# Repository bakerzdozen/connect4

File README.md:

# connect4

## About

4-in-a-line ("Connect 4" by Hasbro) is a popular two-player table game played with red and yellow chips for player 1 and player 2, respectively. It is played on a 7x6 board, where the objective is to connect four of your coloured chips in a row - be that horizontal, vertical or diagonal. 

This project aims to recreate the joy of 4-in-a-line with a modern twist, allowing for solo play against the "computer" (a very basic algorithm). Both the hardware and firmware are included in this repository to allow you to create your own variants or to make the exact same one yourself!

Originally, this project was a Christmas gift for my family and friends, but I have now made it open-source so anyone can make their own, or modify it to make it even better!

## Making Your Own

If you intend to create your own, you will need - at very least - the following:

- STM Cube IDE
- Pre-compiled firmware
- Fully assembled circuit board (I recommend JLC PCB)

## Improvements

If you have suggestions for how to make this project better, please let me know! The best way is through creating your own branch and making the modifications you see fit. If they are sensible and enhance the project in some meaningful way, I will be happy to merge your modifications to the main branch!

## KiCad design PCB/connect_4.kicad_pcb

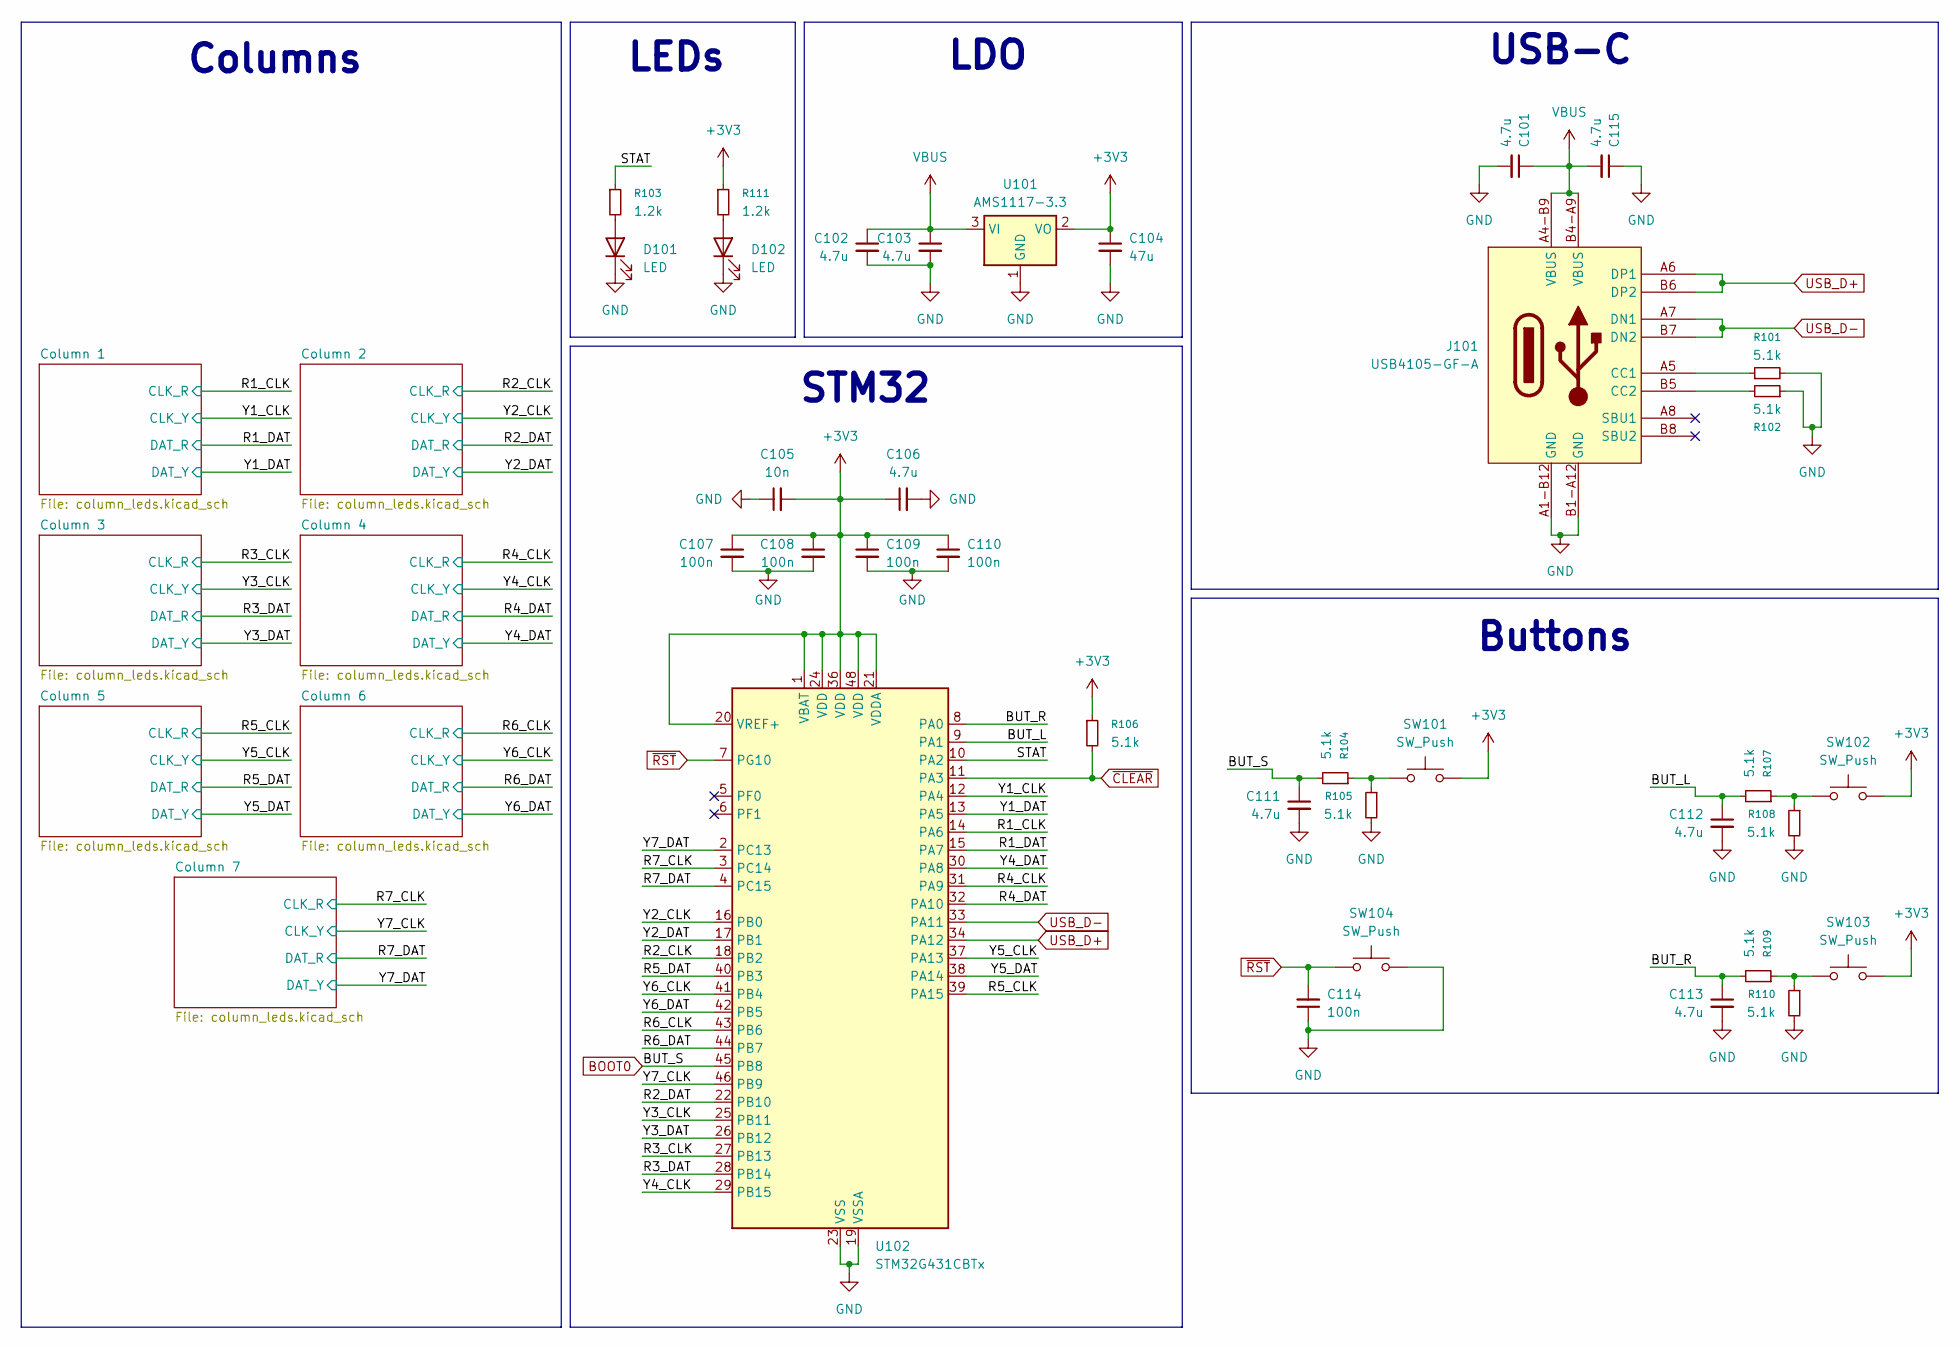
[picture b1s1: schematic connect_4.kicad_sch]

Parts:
C101, C102, C103, C106, C111, C112, C113, C115: 4.7u; C_0603_1608Metric; Manufacturer Part Number C69335
C104: 47u; C_1206_3216Metric; Manufacturer Part Number C403725
C105: 10n; C_0603_1608Metric; Manufacturer Part Number C1589
C107, C108, C109, C110, C114: 100n; C_0603_1608Metric; Manufacturer Part Number C1591
D101, D102: LED; D_0603_1608Metric; Manufacturer Part Number C126319
J101: USB4105-GF-A; USB4105_GCT; Manufacturer Part Number C2765186
R101, R102, R104, R105, R106, R107, R108, R109, R110: 5.1k; R_0603_1608Metric; Manufacturer Part Number C105580
R103, R111: 1.2k; R_0603_1608Metric; Manufacturer Part Number C114605
SW101, SW102, SW103, SW104: SW_Push; SW_Push_1P1T_NO_CK_KSC9xxG; Manufacturer Part Number C2837531
U101: AMS1117-3.3; SOT-223-3_TabPin2; Manufacturer Part Number C6186
U102: STM32G431CBTx; LQFP-48_7x7mm_P0.5mm; Manufacturer Part Number C529355

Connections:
+3V3: C104.1, C105.2, C106.1, C107.1, C108.1, C109.1, C110.1, R106.1, R111.1, SW101.2, SW102.2, SW103.2, U101.2 (VO), U102.1 (VBAT), U102.20 (VREF+), U102.21 (VDDA), U102.24 (VDD), U102.36 (VDD), U102.48 (VDD); also elsewhere on the board
/BUT_L: C112.1, R107.2, U102.9 (PA1)
/BUT_R: C113.1, R109.2, U102.8 (PA0)
/R1_CLK: U102.14 (PA6); also elsewhere on the board
/R1_DAT: U102.15 (PA7); also elsewhere on the board
/R2_CLK: U102.18 (PB2); also elsewhere on the board
/R2_DAT: U102.22 (PB10); also elsewhere on the board
/R3_CLK: U102.27 (PB13); also elsewhere on the board
/R3_DAT: U102.28 (PB14); also elsewhere on the board
/R4_CLK: U102.31 (PA9); also elsewhere on the board
/R4_DAT: U102.32 (PA10); also elsewhere on the board
/R5_CLK: U102.39 (PA15); also elsewhere on the board
/R5_DAT: U102.40 (PB3); also elsewhere on the board
/R6_CLK: U102.43 (PB6); also elsewhere on the board
/R6_DAT: U102.44 (PB7); also elsewhere on the board
/R7_CLK: U102.3 (PC14); also elsewhere on the board
/R7_DAT: U102.4 (PC15); also elsewhere on the board
/STAT: R103.1, U102.10 (PA2)
/Y1_CLK: U102.12 (PA4); also elsewhere on the board
/Y1_DAT: U102.13 (PA5); also elsewhere on the board
/Y2_CLK: U102.16 (PB0); also elsewhere on the board
/Y2_DAT: U102.17 (PB1); also elsewhere on the board
/Y3_CLK: U102.25 (PB11); also elsewhere on the board
/Y3_DAT: U102.26 (PB12); also elsewhere on the board
/Y4_CLK: U102.29 (PB15); also elsewhere on the board
/Y4_DAT: U102.30 (PA8); also elsewhere on the board
/Y5_CLK: U102.37 (PA13); also elsewhere on the board
/Y5_DAT: U102.38 (PA14); also elsewhere on the board
/Y6_CLK: U102.41 (PB4); also elsewhere on the board
/Y6_DAT: U102.42 (PB5); also elsewhere on the board
/Y7_CLK: U102.46 (PB9); also elsewhere on the board
/Y7_DAT: U102.2 (PC13); also elsewhere on the board
BOOT0: C111.1, R104.2, U102.45 (PB8)
GND: C101.2, C102.2, C103.2, C104.2, C105.1, C106.2, C107.2, C108.2, C109.2, C110.2, C111.2, C112.2, C113.2, C114.1, C115.1, D101.1 (K), D102.1 (K), J101.A1-B12 (GND), J101.B1-A12 (GND), R101.2, R102.1, R105.2, R108.2, R110.2, SW104.2, U101.1 (GND), U102.19 (VSSA), U102.23 (VSS), U102.35 (VSS), U102.47 (VSS); also elsewhere on the board
unnamed: D101.2 (A), R103.2
unnamed: D102.2 (A), R111.2
unnamed: J101.A5 (CC1), R101.1
unnamed: J101.B5 (CC2), R102.2
unnamed: R104.1, R105.1, SW101.1
unnamed: R107.1, R108.1, SW102.1
unnamed: R109.1, R110.1, SW103.1
USB_D+: J101.A6 (DP1), J101.B6 (DP2), U102.34 (PA12)
USB_D-: J101.A7 (DN1), J101.B7 (DN2), U102.33 (PA11)
VBUS: C101.1, C102.1, C103.1, C115.2, J101.A4-B9 (VBUS), J101.B4-A9 (VBUS), U101.3 (VI)
~CLEAR: R106.2, U102.11 (PA3); also elsewhere on the board
~RST: C114.2, SW104.1, U102.7 (PG10)

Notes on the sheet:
Buttons
USB-C
LDO
LEDs
STM32
Columns

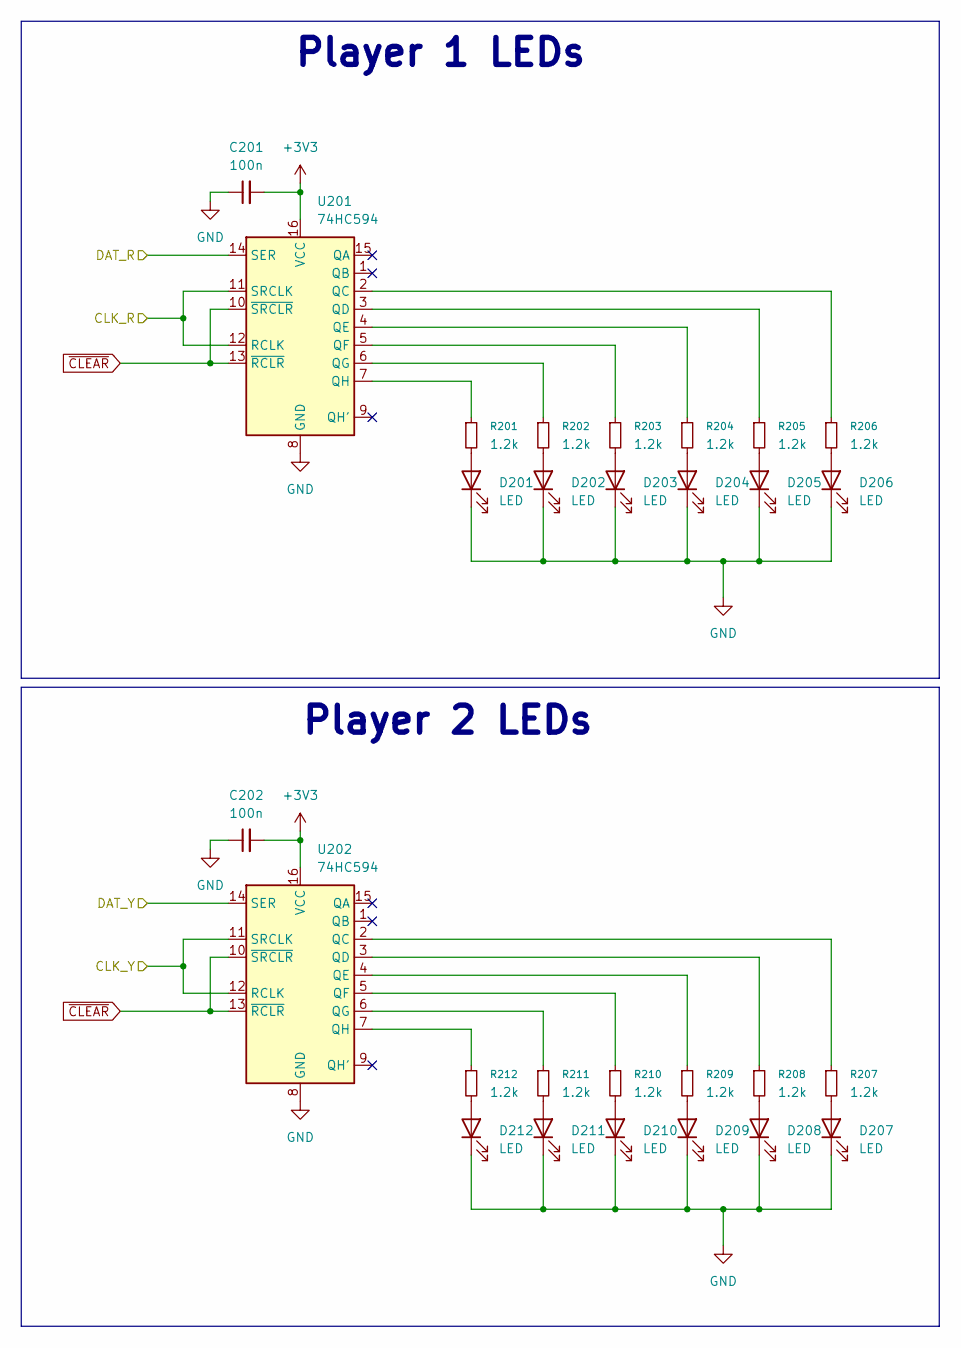
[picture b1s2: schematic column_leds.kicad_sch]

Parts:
C201, C202: 100n; C_0603_1608Metric; Manufacturer Part Number C1591
D201, D202, D203, D204, D205, D206: LED; D_0603_1608Metric; Manufacturer Part Number C79636
D207, D208, D209, D210, D211, D212: LED; D_0603_1608Metric; Manufacturer Part Number C122984
R201, R202, R203, R204, R205, R206, R207, R208, R209, R210, R211, R212: 1.2k; R_0603_1608Metric; Manufacturer Part Number C114605
U201, U202: 74HC594; SOIC-16W_5.3x10.2mm_P1.27mm; Manufacturer Part Number C91727

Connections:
+3V3: C201.2, C202.2, U201.16 (VCC), U202.16 (VCC); also elsewhere on the board
/R1_CLK: U201.11 (SRCLK), U201.12 (RCLK); also elsewhere on the board
/R1_DAT: U201.14 (SER); also elsewhere on the board
/Y1_CLK: U202.11 (SRCLK), U202.12 (RCLK); also elsewhere on the board
/Y1_DAT: U202.14 (SER); also elsewhere on the board
GND: C201.1, C202.1, D201.1 (K), D202.1 (K), D203.1 (K), D204.1 (K), D205.1 (K), D206.1 (K), D207.1 (K), D208.1 (K), D209.1 (K), D210.1 (K), D211.1 (K), D212.1 (K), U201.8 (GND), U202.8 (GND); also elsewhere on the board
unnamed: D201.2 (A), R201.2
unnamed: D202.2 (A), R202.2
unnamed: D203.2 (A), R203.2
unnamed: D204.2 (A), R204.2
unnamed: D205.2 (A), R205.2
unnamed: D206.2 (A), R206.2
unnamed: D207.2 (A), R207.2
unnamed: D208.2 (A), R208.2
unnamed: D209.2 (A), R209.2
unnamed: D210.2 (A), R210.2
unnamed: D211.2 (A), R211.2
unnamed: D212.2 (A), R212.2
unnamed: R206.1, U201.2 (QC)
unnamed: R205.1, U201.3 (QD)
unnamed: R204.1, U201.4 (QE)
unnamed: R203.1, U201.5 (QF)
unnamed: R202.1, U201.6 (QG)
unnamed: R201.1, U201.7 (QH)
unnamed: R207.1, U202.2 (QC)
unnamed: R208.1, U202.3 (QD)
unnamed: R209.1, U202.4 (QE)
unnamed: R210.1, U202.5 (QF)
unnamed: R211.1, U202.6 (QG)
unnamed: R212.1, U202.7 (QH)
~CLEAR: U201.10 (~SRCLR), U201.13 (~RCLR), U202.10 (~SRCLR), U202.13 (~RCLR); also elsewhere on the board

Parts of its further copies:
C301, C302, C401, C402, C501, C502, C601, C602, C701, C702, C801, C802: 100n; C_0603_1608Metric; Manufacturer Part Number C1591
D301, D302, D303, D304, D305, D306, D401, D402, D403, D404, D405, D406, D501, D502, D503, D504, D505, D506, D601, D602, D603, D604, D605, D606, D701, D702, D703, D704, D705, D706, D801, D802, D803, D804, D805, D806: LED; D_0603_1608Metric; Manufacturer Part Number C79636
D307, D308, D309, D310, D311, D312, D407, D408, D409, D410, D411, D412, D507, D508, D509, D510, D511, D512, D607, D608, D609, D610, D611, D612, D707, D708, D709, D710, D711, D712, D807, D808, D809, D810, D811, D812: LED; D_0603_1608Metric; Manufacturer Part Number C122984
R301, R302, R303, R304, R305, R306, R307, R308, R309, R310, R311, R312, R401, R402, R403, R404, R405, R406, R407, R408, R409, R410, R411, R412, R501, R502, R503, R504, R505, R506, R507, R508, R509, R510, R511, R512, R601, R602, R603, R604, R605, R606, R607, R608, R609, R610, R611, R612, R701, R702, R703, R704, R705, R706, R707, R708, R709, R710, R711, R712, R801, R802, R803, R804, R805, R806, R807, R808, R809, R810, R811, R812: 1.2k; R_0603_1608Metric; Manufacturer Part Number C114605
U301, U302, U401, U402, U501, U502, U601, U602, U701, U702, U801, U802: 74HC594; SOIC-16W_5.3x10.2mm_P1.27mm; Manufacturer Part Number C91727

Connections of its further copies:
+3V3: C301.2, C302.2, C401.2, C402.2, C501.2, C502.2, C601.2, C602.2, C701.2, C702.2, C801.2, C802.2, U301.16 (VCC), U302.16 (VCC), U401.16 (VCC), U402.16 (VCC), U501.16 (VCC), U502.16 (VCC), U601.16 (VCC), U602.16 (VCC), U701.16 (VCC), U702.16 (VCC), U801.16 (VCC), U802.16 (VCC); also elsewhere on the board
/R2_CLK: U301.11 (SRCLK), U301.12 (RCLK); also elsewhere on the board
/R2_DAT: U301.14 (SER); also elsewhere on the board
/R3_CLK: U401.11 (SRCLK), U401.12 (RCLK); also elsewhere on the board
/R3_DAT: U401.14 (SER); also elsewhere on the board
/R4_CLK: U501.11 (SRCLK), U501.12 (RCLK); also elsewhere on the board
/R4_DAT: U501.14 (SER); also elsewhere on the board
/R5_CLK: U601.11 (SRCLK), U601.12 (RCLK); also elsewhere on the board
/R5_DAT: U601.14 (SER); also elsewhere on the board
/R6_CLK: U701.11 (SRCLK), U701.12 (RCLK); also elsewhere on the board
/R6_DAT: U701.14 (SER); also elsewhere on the board
/R7_CLK: U801.11 (SRCLK), U801.12 (RCLK); also elsewhere on the board
/R7_DAT: U801.14 (SER); also elsewhere on the board
/Y2_CLK: U302.11 (SRCLK), U302.12 (RCLK); also elsewhere on the board
/Y2_DAT: U302.14 (SER); also elsewhere on the board
/Y3_CLK: U402.11 (SRCLK), U402.12 (RCLK); also elsewhere on the board
/Y3_DAT: U402.14 (SER); also elsewhere on the board
/Y4_CLK: U502.11 (SRCLK), U502.12 (RCLK); also elsewhere on the board
/Y4_DAT: U502.14 (SER); also elsewhere on the board
/Y5_CLK: U602.11 (SRCLK), U602.12 (RCLK); also elsewhere on the board
/Y5_DAT: U602.14 (SER); also elsewhere on the board
/Y6_CLK: U702.11 (SRCLK), U702.12 (RCLK); also elsewhere on the board
/Y6_DAT: U702.14 (SER); also elsewhere on the board
/Y7_CLK: U802.11 (SRCLK), U802.12 (RCLK); also elsewhere on the board
/Y7_DAT: U802.14 (SER); also elsewhere on the board
GND: C301.1, C302.1, C401.1, C402.1, C501.1, C502.1, C601.1, C602.1, C701.1, C702.1, C801.1, C802.1, D301.1 (K), D302.1 (K), D303.1 (K), D304.1 (K), D305.1 (K), D306.1 (K), D307.1 (K), D308.1 (K), D309.1 (K), D310.1 (K), D311.1 (K), D312.1 (K), D401.1 (K), D402.1 (K), D403.1 (K), D404.1 (K), D405.1 (K), D406.1 (K), D407.1 (K), D408.1 (K), D409.1 (K), D410.1 (K), D411.1 (K), D412.1 (K), D501.1 (K), D502.1 (K), D503.1 (K), D504.1 (K), D505.1 (K), D506.1 (K), D507.1 (K), D508.1 (K), D509.1 (K), D510.1 (K), D511.1 (K), D512.1 (K), D601.1 (K), D602.1 (K), D603.1 (K), D604.1 (K), D605.1 (K), D606.1 (K), D607.1 (K), D608.1 (K), D609.1 (K), D610.1 (K), D611.1 (K), D612.1 (K), D701.1 (K), D702.1 (K), D703.1 (K), D704.1 (K), D705.1 (K), D706.1 (K), D707.1 (K), D708.1 (K), D709.1 (K), D710.1 (K), D711.1 (K), D712.1 (K), D801.1 (K), D802.1 (K), D803.1 (K), D804.1 (K), D805.1 (K), D806.1 (K), D807.1 (K), D808.1 (K), D809.1 (K), D810.1 (K), D811.1 (K), D812.1 (K), U301.8 (GND), U302.8 (GND), U401.8 (GND), U402.8 (GND), U501.8 (GND), U502.8 (GND), U601.8 (GND), U602.8 (GND), U701.8 (GND), U702.8 (GND), U801.8 (GND), U802.8 (GND); also elsewhere on the board
unnamed: D301.2 (A), R301.2
unnamed: D302.2 (A), R302.2
unnamed: D303.2 (A), R303.2
unnamed: D304.2 (A), R304.2
unnamed: D305.2 (A), R305.2
unnamed: D306.2 (A), R306.2
unnamed: D307.2 (A), R307.2
unnamed: D308.2 (A), R308.2
unnamed: D309.2 (A), R309.2
unnamed: D310.2 (A), R310.2
unnamed: D311.2 (A), R311.2
unnamed: D312.2 (A), R312.2
unnamed: D401.2 (A), R401.2
unnamed: D402.2 (A), R402.2
unnamed: D403.2 (A), R403.2
unnamed: D404.2 (A), R404.2
unnamed: D405.2 (A), R405.2
unnamed: D406.2 (A), R406.2
unnamed: D407.2 (A), R407.2
unnamed: D408.2 (A), R408.2
unnamed: D409.2 (A), R409.2
unnamed: D410.2 (A), R410.2
unnamed: D411.2 (A), R411.2
unnamed: D412.2 (A), R412.2
unnamed: D501.2 (A), R501.2
unnamed: D502.2 (A), R502.2
unnamed: D503.2 (A), R503.2
unnamed: D504.2 (A), R504.2
unnamed: D505.2 (A), R505.2
unnamed: D506.2 (A), R506.2
unnamed: D507.2 (A), R507.2
unnamed: D508.2 (A), R508.2
unnamed: D509.2 (A), R509.2
unnamed: D510.2 (A), R510.2
unnamed: D511.2 (A), R511.2
unnamed: D512.2 (A), R512.2
unnamed: D601.2 (A), R601.2
unnamed: D602.2 (A), R602.2
unnamed: D603.2 (A), R603.2
unnamed: D604.2 (A), R604.2
unnamed: D605.2 (A), R605.2
unnamed: D606.2 (A), R606.2
unnamed: D607.2 (A), R607.2
unnamed: D608.2 (A), R608.2
unnamed: D609.2 (A), R609.2
unnamed: D610.2 (A), R610.2
unnamed: D611.2 (A), R611.2
unnamed: D612.2 (A), R612.2
unnamed: D701.2 (A), R701.2
unnamed: D702.2 (A), R702.2
unnamed: D703.2 (A), R703.2
unnamed: D704.2 (A), R704.2
unnamed: D705.2 (A), R705.2
unnamed: D706.2 (A), R706.2
unnamed: D707.2 (A), R707.2
unnamed: D708.2 (A), R708.2
unnamed: D709.2 (A), R709.2
unnamed: D710.2 (A), R710.2
unnamed: D711.2 (A), R711.2
unnamed: D712.2 (A), R712.2
unnamed: D801.2 (A), R801.2
unnamed: D802.2 (A), R802.2
unnamed: D803.2 (A), R803.2
unnamed: D804.2 (A), R804.2
unnamed: D805.2 (A), R805.2
unnamed: D806.2 (A), R806.2
unnamed: D807.2 (A), R807.2
unnamed: D808.2 (A), R808.2
unnamed: D809.2 (A), R809.2
unnamed: D810.2 (A), R810.2
unnamed: D811.2 (A), R811.2
unnamed: D812.2 (A), R812.2
unnamed: R306.1, U301.2 (QC)
unnamed: R305.1, U301.3 (QD)
unnamed: R304.1, U301.4 (QE)
unnamed: R303.1, U301.5 (QF)
unnamed: R302.1, U301.6 (QG)
unnamed: R301.1, U301.7 (QH)
unnamed: R307.1, U302.2 (QC)
unnamed: R308.1, U302.3 (QD)
unnamed: R309.1, U302.4 (QE)
unnamed: R310.1, U302.5 (QF)
unnamed: R311.1, U302.6 (QG)
unnamed: R312.1, U302.7 (QH)
unnamed: R406.1, U401.2 (QC)
unnamed: R405.1, U401.3 (QD)
unnamed: R404.1, U401.4 (QE)
unnamed: R403.1, U401.5 (QF)
unnamed: R402.1, U401.6 (QG)
unnamed: R401.1, U401.7 (QH)
unnamed: R407.1, U402.2 (QC)
unnamed: R408.1, U402.3 (QD)
unnamed: R409.1, U402.4 (QE)
unnamed: R410.1, U402.5 (QF)
unnamed: R411.1, U402.6 (QG)
unnamed: R412.1, U402.7 (QH)
unnamed: R506.1, U501.2 (QC)
unnamed: R505.1, U501.3 (QD)
unnamed: R504.1, U501.4 (QE)
unnamed: R503.1, U501.5 (QF)
unnamed: R502.1, U501.6 (QG)
unnamed: R501.1, U501.7 (QH)
unnamed: R507.1, U502.2 (QC)
unnamed: R508.1, U502.3 (QD)
unnamed: R509.1, U502.4 (QE)
unnamed: R510.1, U502.5 (QF)
unnamed: R511.1, U502.6 (QG)
unnamed: R512.1, U502.7 (QH)
unnamed: R606.1, U601.2 (QC)
unnamed: R605.1, U601.3 (QD)
unnamed: R604.1, U601.4 (QE)
unnamed: R603.1, U601.5 (QF)
unnamed: R602.1, U601.6 (QG)
unnamed: R601.1, U601.7 (QH)
unnamed: R607.1, U602.2 (QC)
unnamed: R608.1, U602.3 (QD)
unnamed: R609.1, U602.4 (QE)
unnamed: R610.1, U602.5 (QF)
unnamed: R611.1, U602.6 (QG)
unnamed: R612.1, U602.7 (QH)
unnamed: R706.1, U701.2 (QC)
unnamed: R705.1, U701.3 (QD)
unnamed: R704.1, U701.4 (QE)
unnamed: R703.1, U701.5 (QF)
unnamed: R702.1, U701.6 (QG)
unnamed: R701.1, U701.7 (QH)
unnamed: R707.1, U702.2 (QC)
unnamed: R708.1, U702.3 (QD)
unnamed: R709.1, U702.4 (QE)
unnamed: R710.1, U702.5 (QF)
unnamed: R711.1, U702.6 (QG)
unnamed: R712.1, U702.7 (QH)
unnamed: R806.1, U801.2 (QC)
unnamed: R805.1, U801.3 (QD)
unnamed: R804.1, U801.4 (QE)
unnamed: R803.1, U801.5 (QF)
unnamed: R802.1, U801.6 (QG)
unnamed: R801.1, U801.7 (QH)
unnamed: R807.1, U802.2 (QC)
unnamed: R808.1, U802.3 (QD)
unnamed: R809.1, U802.4 (QE)
unnamed: R810.1, U802.5 (QF)
unnamed: R811.1, U802.6 (QG)
unnamed: R812.1, U802.7 (QH)
~CLEAR: U301.10 (~SRCLR), U301.13 (~RCLR), U302.10 (~SRCLR), U302.13 (~RCLR), U401.10 (~SRCLR), U401.13 (~RCLR), U402.10 (~SRCLR), U402.13 (~RCLR), U501.10 (~SRCLR), U501.13 (~RCLR), U502.10 (~SRCLR), U502.13 (~RCLR), U601.10 (~SRCLR), U601.13 (~RCLR), U602.10 (~SRCLR), U602.13 (~RCLR), U701.10 (~SRCLR), U701.13 (~RCLR), U702.10 (~SRCLR), U702.13 (~RCLR), U801.10 (~SRCLR), U801.13 (~RCLR), U802.10 (~SRCLR), U802.13 (~RCLR); also elsewhere on the board

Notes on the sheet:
Player 2 LEDs
Player 1 LEDs

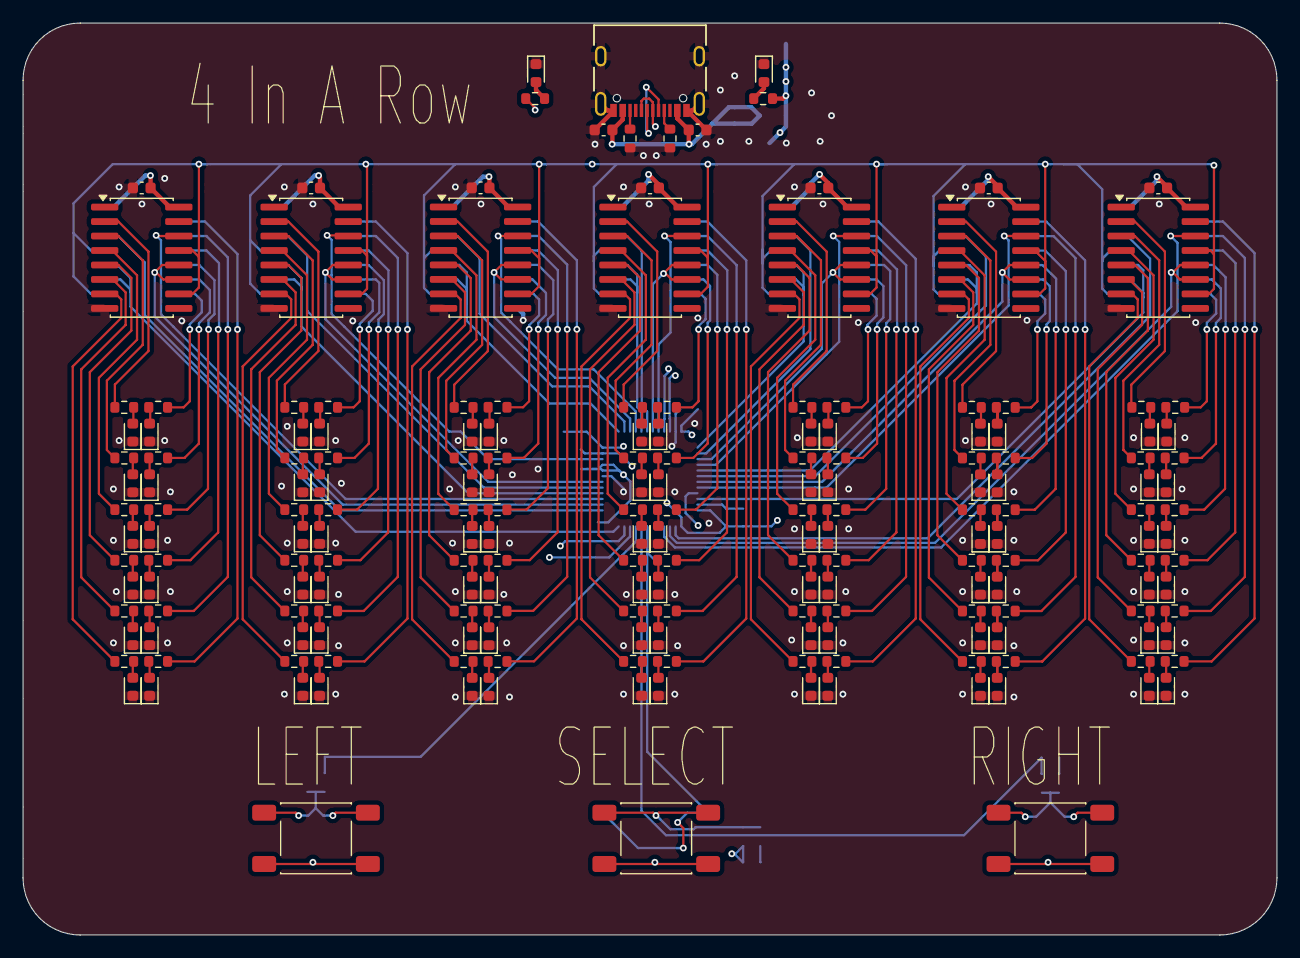
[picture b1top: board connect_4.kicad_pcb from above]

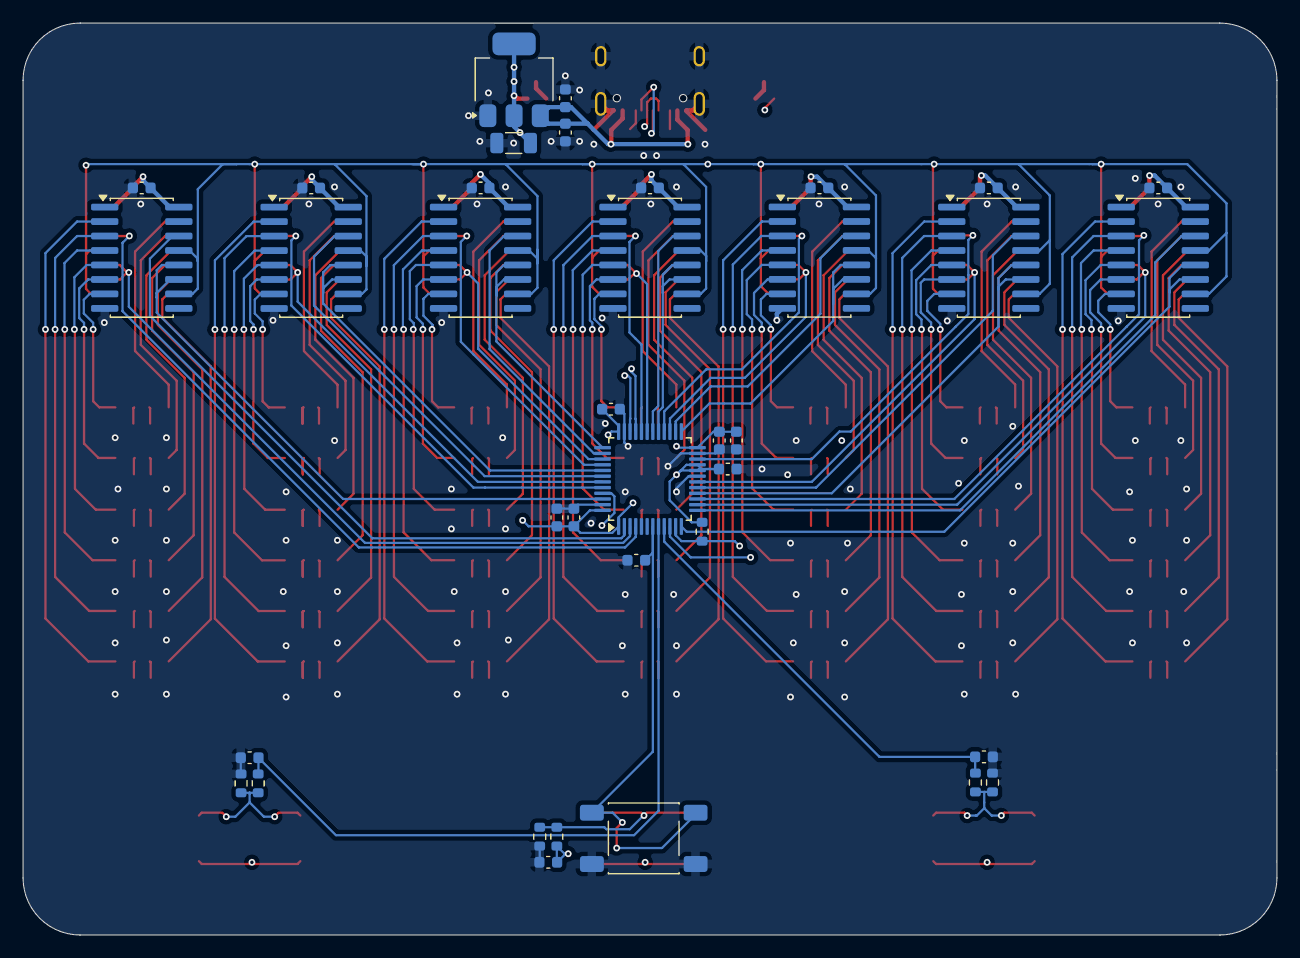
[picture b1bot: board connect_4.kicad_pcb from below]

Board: 4 copper layers, 110.0 x 80.0 mm, 231 parts (37 on the bottom side), 214 nets.

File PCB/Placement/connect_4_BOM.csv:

Designator,Qty,Comment,Footprint,JLC Part Number
"C101,C102,C103,C106,C111,C112,C113,C115",8,4.7u,Capacitor_SMD:C_0603_1608Metric,C69335
C104,1,47u,Capacitor_SMD:C_1206_3216Metric,C403725
C105,1,10n,Capacitor_SMD:C_0603_1608Metric,C1589
"C107,C108,C109,C110,C114,C201,C202,C301,C302,C401,C402,C501,C502,C601,C602,C701,C702,C801,C802",19,100n,Capacitor_SMD:C_0603_1608Metric,C1591
"D101,D102",2,LED,Diode_SMD:D_0603_1608Metric,C126319
"D201,D202,D203,D204,D205,D206,D301,D302,D303,D304,D305,D306,D401,D402,D403,D404,D405,D406,D501,D502,D503,D504,D505,D506,D601,D602,D603,D604,D605,D606,D701,D702,D703,D704,D705,D706,D801,D802,D803,D804,D805,D806",42,LED,Diode_SMD:D_0603_1608Metric,C79636
"D207,D208,D209,D210,D211,D212,D307,D308,D309,D310,D311,D312,D407,D408,D409,D410,D411,D412,D507,D508,D509,D510,D511,D512,D607,D608,D609,D610,D611,D612,D707,D708,D709,D710,D711,D712,D807,D808,D809,D810,D811,D812",42,LED,Diode_SMD:D_0603_1608Metric,C122984
J101,1,USB4105-GF-A,Custom:USB4105_GCT,C2765186
"R101,R102,R104,R105,R106,R107,R108,R109,R110",9,5.1k,Resistor_SMD:R_0603_1608Metric,C105580
"R103,R111,R201,R202,R203,R204,R205,R206,R207,R208,R209,R210,R211,R212,R301,R302,R303,R304,R305,R306,R307,R308,R309,R310,R311,R312,R401,R402,R403,R404,R405,R406,R407,R408,R409,R410,R411,R412,R501,R502,R503,R504,R505,R506,R507,R508,R509,R510,R511,R512,R601,R602,R603,R604,R605,R606,R607,R608,R609,R610,R611,R612,R701,R702,R703,R704,R705,R706,R707,R708,R709,R710,R711,R712,R801,R802,R803,R804,R805,R806,R807,R808,R809,R810,R811,R812",86,1.2k,Resistor_SMD:R_0603_1608Metric,C114605
"SW101,SW102,SW103,SW104",4,SW_Push,Button_Switch_SMD:SW_Push_1P1T_NO_CK_KSC9xxG,C2837531
U101,1,AMS1117-3.3,Package_TO_SOT_SMD:SOT-223-3_TabPin2,C6186
U102,1,STM32G431CBTx,Package_QFP:LQFP-48_7x7mm_P0.5mm,C529355
"U201,U202,U301,U302,U401,U402,U501,U502,U601,U602,U701,U702,U801,U802",14,74HC594,Package_SO:SOIC-16W_7.5x10.3mm_P1.27mm,C91727

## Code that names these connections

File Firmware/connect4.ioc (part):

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Mcu.Name=STM32G431C(6-8-B)Tx
Mcu.Package=LQFP48
Mcu.UserName=STM32G431C8Tx
PA0.Signal=GPIO_Input
PA1.Signal=GPIO_Input
PA10.Signal=GPIO_Output
PA11.Mode=Device
PA11.Signal=USB_DM
PA12.Mode=Device
PA12.Signal=USB_DP
PA13.Signal=GPIO_Output
PA14.Signal=GPIO_Output
PA15.Signal=GPIO_Output
PA2.Signal=GPIO_Output
PA3.Signal=GPIO_Output
PA4.Signal=GPIO_Output
PA5.Signal=GPIO_Output
PA6.Signal=GPIO_Output
PA7.Signal=GPIO_Output
PA8.Signal=GPIO_Output
PA9.Signal=GPIO_Output
PB0.Signal=GPIO_Output
PB1.Signal=GPIO_Output
PB10.Signal=GPIO_Output
PB11.Signal=GPIO_Output
PB12.Signal=GPIO_Output
PB13.Signal=GPIO_Output
PB14.Signal=GPIO_Output
PB15.Signal=GPIO_Output
PB2.Signal=GPIO_Output
PB3.Signal=GPIO_Output
PB4.Signal=GPIO_Output
PB5.Signal=GPIO_Output
PB6.Signal=GPIO_Output
PB7.Signal=GPIO_Output
PB8-BOOT0.Signal=GPIO_Input
PB9.Signal=GPIO_Output
PC13.Signal=GPIO_Output
PC14-OSC32_IN.Signal=GPIO_Output
PC15-OSC32_OUT.Signal=GPIO_Output
RCC.HSE_VALUE=8000000
RCC.SYSCLKFreq_VALUE=16000000
board=custom

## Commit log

2025-12-27 Initial POC
2026-02-25 Add PCB file, create README
2026-02-25 Move hidden files to appropriate folders
